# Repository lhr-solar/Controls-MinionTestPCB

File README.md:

# Controls-MinionTestPCB

[Quality Assurance Checklist(QUAC)](PULL_REQUEST_TEMPLATE.md)

[BOM](https://www.mouser.com/ProjectManager/ProjectDetail.aspx?AccessID=bacd2a80e1)

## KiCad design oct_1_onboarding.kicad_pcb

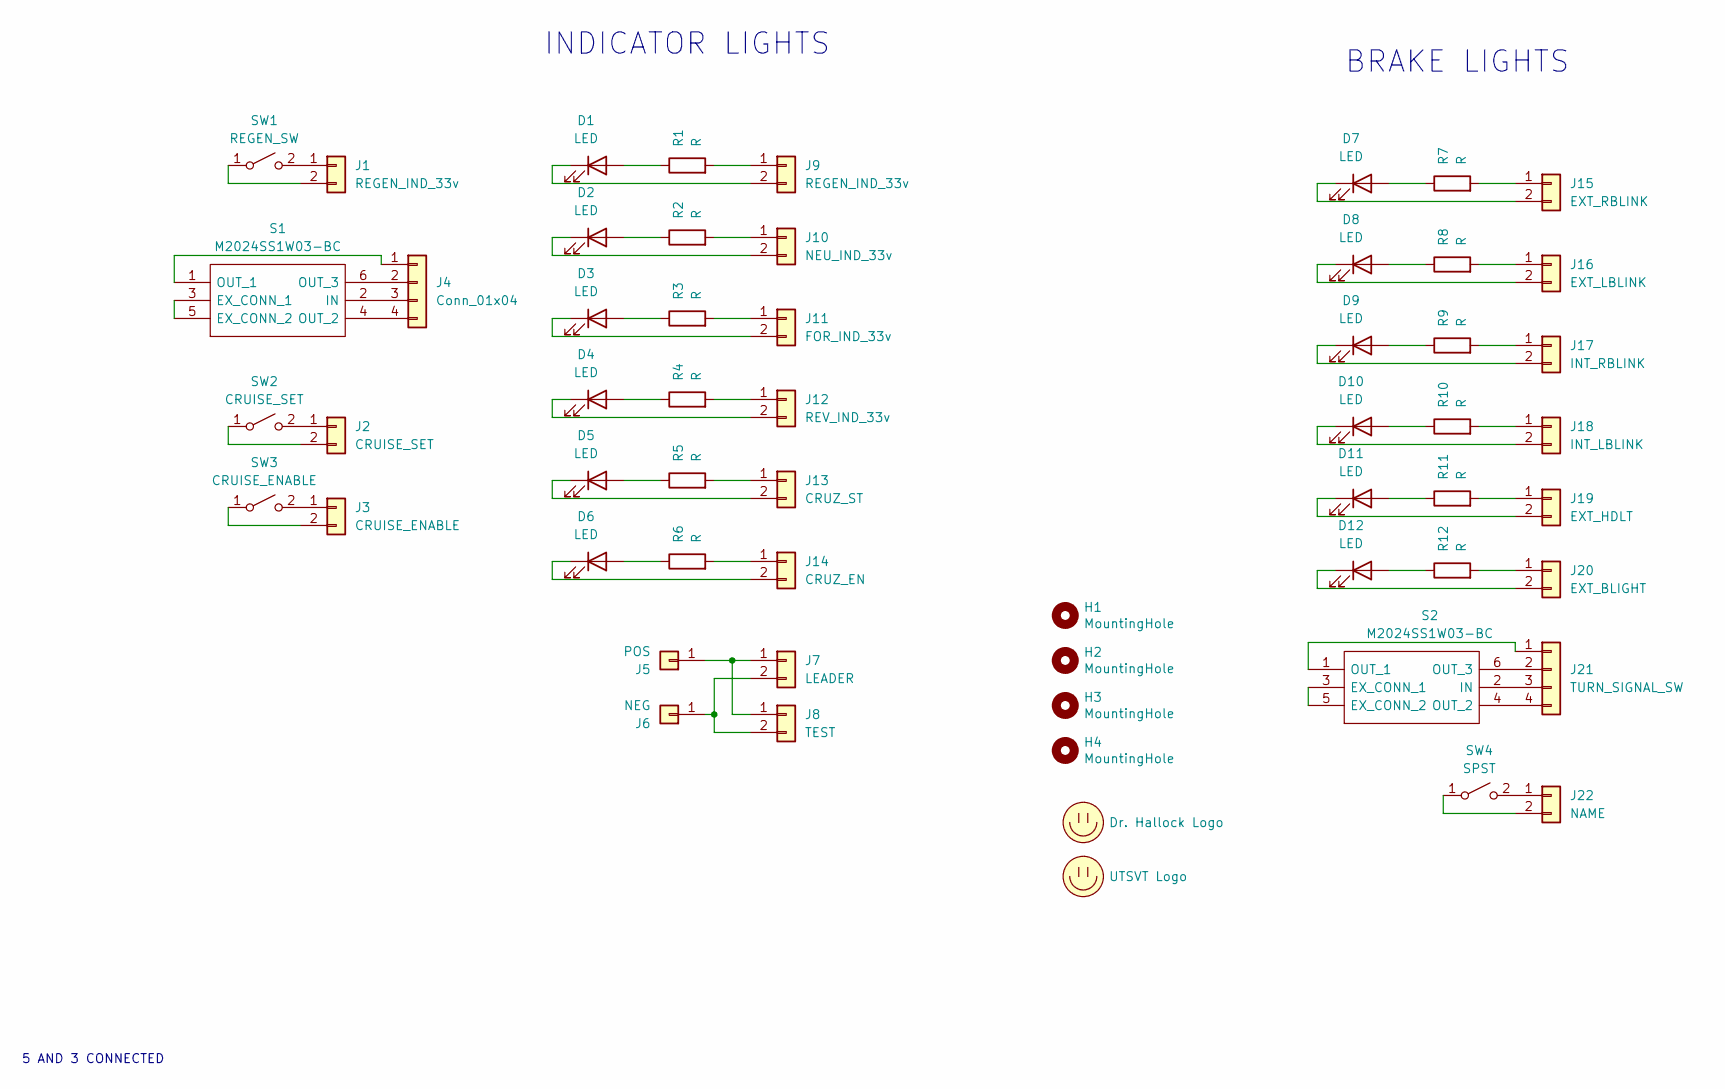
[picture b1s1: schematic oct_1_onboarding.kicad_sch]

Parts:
D1, D2, D3, D4, D5, D6, D7, D8, D9, D10, D11, D12: LED; LED_0805_2012Metric
H1, H2, H3, H4: MountingHole; MountingHole_3mm
J1, J9: REGEN_IND_33v; Molex_Micro-Fit_3.0_43650-0200_1x02_P3.00mm_Horizontal
J2: CRUISE_SET; Molex_Micro-Fit_3.0_43650-0200_1x02_P3.00mm_Horizontal
J3: CRUISE_ENABLE; Molex_Micro-Fit_3.0_43650-0200_1x02_P3.00mm_Horizontal
J4: Conn_01x04; Molex_Micro-Fit_3.0_43650-0400_1x04_P3.00mm_Horizontal
J5: POS; Banana_Jack_1_Pin_4mm
J6: NEG; Banana_Jack_1_Pin_4mm
J7: LEADER; Molex_Micro-Fit_3.0_43650-0200_1x02_P3.00mm_Horizontal
J8: TEST; Molex_Micro-Fit_3.0_43650-0200_1x02_P3.00mm_Horizontal
J10: NEU_IND_33v; Molex_Micro-Fit_3.0_43650-0200_1x02_P3.00mm_Horizontal
J11: FOR_IND_33v; Molex_Micro-Fit_3.0_43650-0200_1x02_P3.00mm_Horizontal
J12: REV_IND_33v; Molex_Micro-Fit_3.0_43650-0200_1x02_P3.00mm_Horizontal
J13: CRUZ_ST; Molex_Micro-Fit_3.0_43650-0200_1x02_P3.00mm_Horizontal
J14: CRUZ_EN; Molex_Micro-Fit_3.0_43650-0200_1x02_P3.00mm_Horizontal
J15: EXT_RBLINK; Molex_Micro-Fit_3.0_43650-0200_1x02_P3.00mm_Horizontal
J16: EXT_LBLINK; Molex_Micro-Fit_3.0_43650-0200_1x02_P3.00mm_Horizontal
J17: INT_RBLINK; Molex_Micro-Fit_3.0_43650-0200_1x02_P3.00mm_Horizontal
J18: INT_LBLINK; Molex_Micro-Fit_3.0_43650-0200_1x02_P3.00mm_Horizontal
J19: EXT_HDLT; Molex_Micro-Fit_3.0_43650-0200_1x02_P3.00mm_Horizontal
J20: EXT_BLIGHT; Molex_Micro-Fit_3.0_43650-0200_1x02_P3.00mm_Horizontal
J21: TURN_SIGNAL_SW; Molex_Micro-Fit_3.0_43650-0400_1x04_P3.00mm_Horizontal
J22: NAME; Molex_Micro-Fit_3.0_43650-0200_1x02_P3.00mm_Horizontal
LOGO1: Dr. Hallock Logo; Hallock_Image_Tiny
LOGO2: UTSVT Logo; UTSVT_Logo_Symbol
R1, R2, R3, R4, R5, R6, R7, R8, R9, R10, R11, R12: R; R_0805_2012Metric
S1, S2: M2024SS1W03-BC; M2024SS1W03BC; Mouser Part Number 633-M2024SS1W03-BC
SW1: REGEN_SW; 2MS6T1B3M2QES
SW2: CRUISE_SET; 2MS6T1B3M2QES
SW3: CRUISE_ENABLE; 2MS6T1B3M2QES
SW4: SPST; 2MS6T1B3M2QES

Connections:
unnamed: D1.1 (K), J9.2
unnamed: D1.2 (A), R1.1
unnamed: D2.1 (K), J10.2
unnamed: D2.2 (A), R2.1
unnamed: D3.1 (K), J11.2
unnamed: D3.2 (A), R3.1
unnamed: D4.1 (K), J12.2
unnamed: D4.2 (A), R4.1
unnamed: D5.1 (K), J13.2
unnamed: D5.2 (A), R5.1
unnamed: D6.1 (K), J14.2
unnamed: D6.2 (A), R6.1
unnamed: D7.1 (K), J15.2
unnamed: D7.2 (A), R7.1
unnamed: D8.1 (K), J16.2
unnamed: D8.2 (A), R8.1
unnamed: D9.1 (K), J17.2
unnamed: D9.2 (A), R9.1
unnamed: D10.1 (K), J18.2
unnamed: D10.2 (A), R10.1
unnamed: D11.1 (K), J19.2
unnamed: D11.2 (A), R11.1
unnamed: D12.1 (K), J20.2
unnamed: D12.2 (A), R12.1
unnamed: J1.1, SW1.2 (B)
unnamed: J1.2, SW1.1 (A)
unnamed: J2.1, SW2.2 (B)
unnamed: J2.2, SW2.1 (A)
unnamed: J3.1, SW3.2 (B)
unnamed: J3.2, SW3.1 (A)
unnamed: J4.1, S1.1 (OUT_1)
unnamed: J4.2, S1.6 (OUT_3)
unnamed: J4.3, S1.2 (IN)
unnamed: J4.4, S1.4 (OUT_2)
unnamed: J5.1, J7.1, J8.1
unnamed: J6.1, J7.2, J8.2
unnamed: J9.1, R1.2
unnamed: J10.1, R2.2
unnamed: J11.1, R3.2
unnamed: J12.1, R4.2
unnamed: J13.1, R5.2
unnamed: J14.1, R6.2
unnamed: J15.1, R7.2
unnamed: J16.1, R8.2
unnamed: J17.1, R9.2
unnamed: J18.1, R10.2
unnamed: J19.1, R11.2
unnamed: J20.1, R12.2
unnamed: J21.1, S2.1 (OUT_1)
unnamed: J21.2, S2.6 (OUT_3)
unnamed: J21.3, S2.2 (IN)
unnamed: J21.4, S2.4 (OUT_2)
unnamed: J22.1, SW4.2 (B)
unnamed: J22.2, SW4.1 (A)
unnamed: S1.3 (EX_CONN_1), S1.5 (EX_CONN_2)
unnamed: S2.3 (EX_CONN_1), S2.5 (EX_CONN_2)

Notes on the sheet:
INDICATOR LIGHTS
5 AND 3 CONNECTED
BRAKE LIGHTS

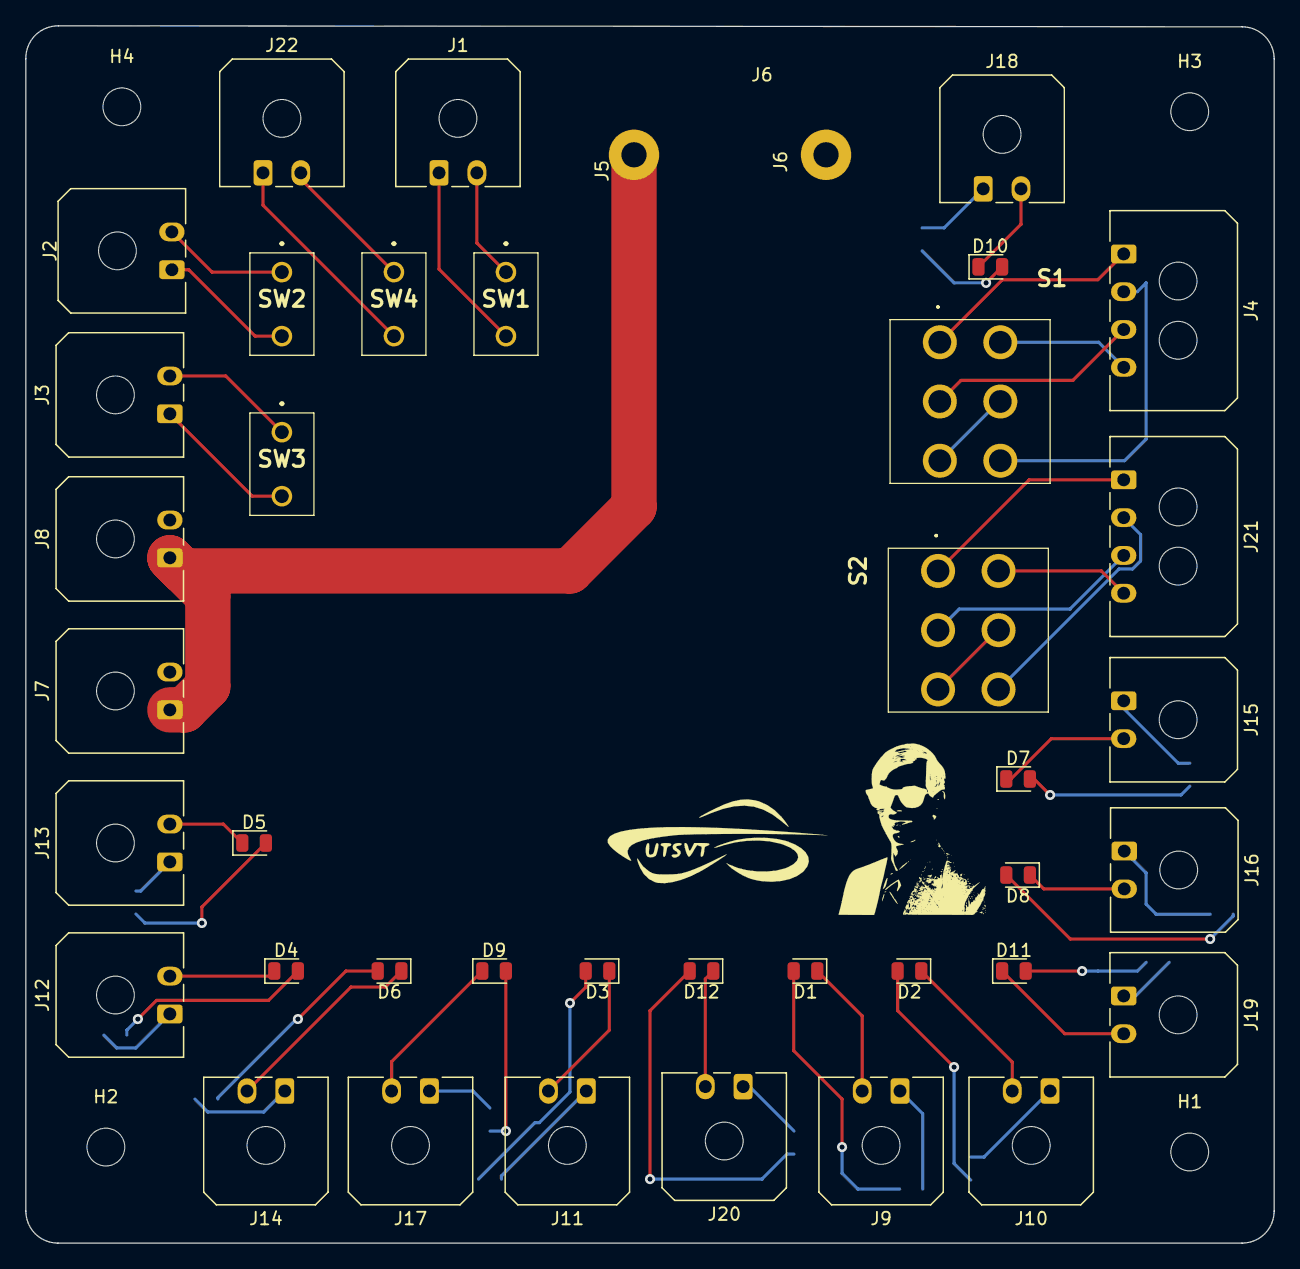
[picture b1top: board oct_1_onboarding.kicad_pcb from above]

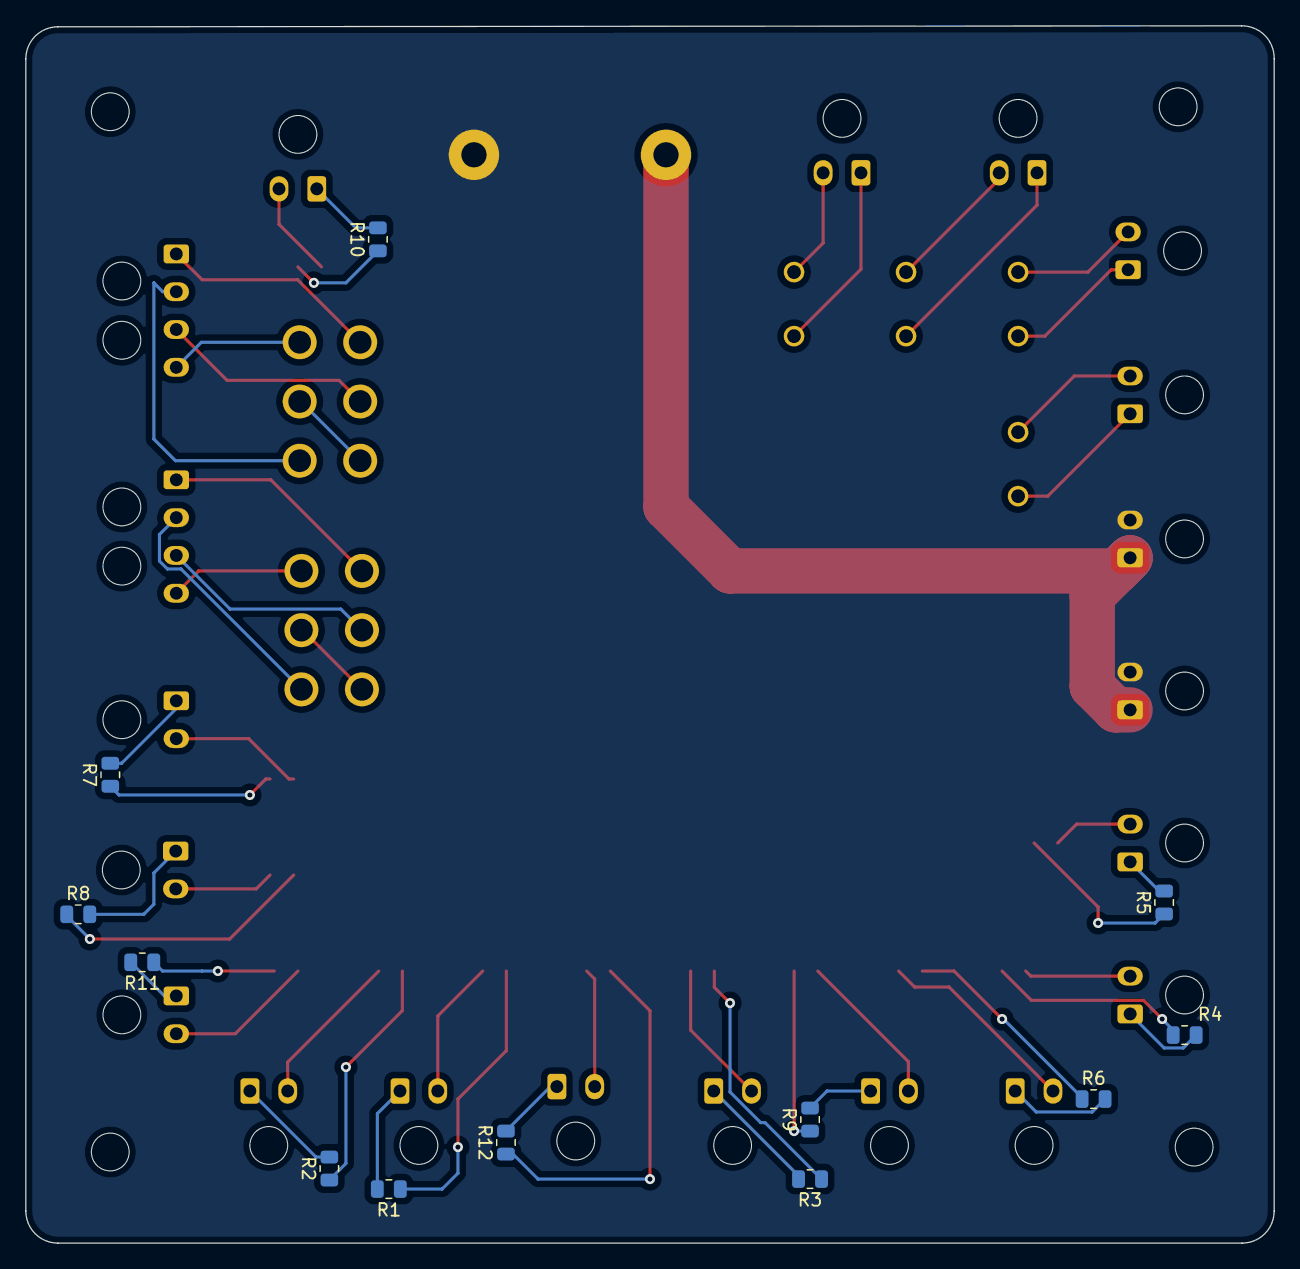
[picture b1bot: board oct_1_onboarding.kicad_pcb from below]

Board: 2 copper layers, 99.1 x 96.6 mm, 58 parts (12 on the bottom side), 56 nets.

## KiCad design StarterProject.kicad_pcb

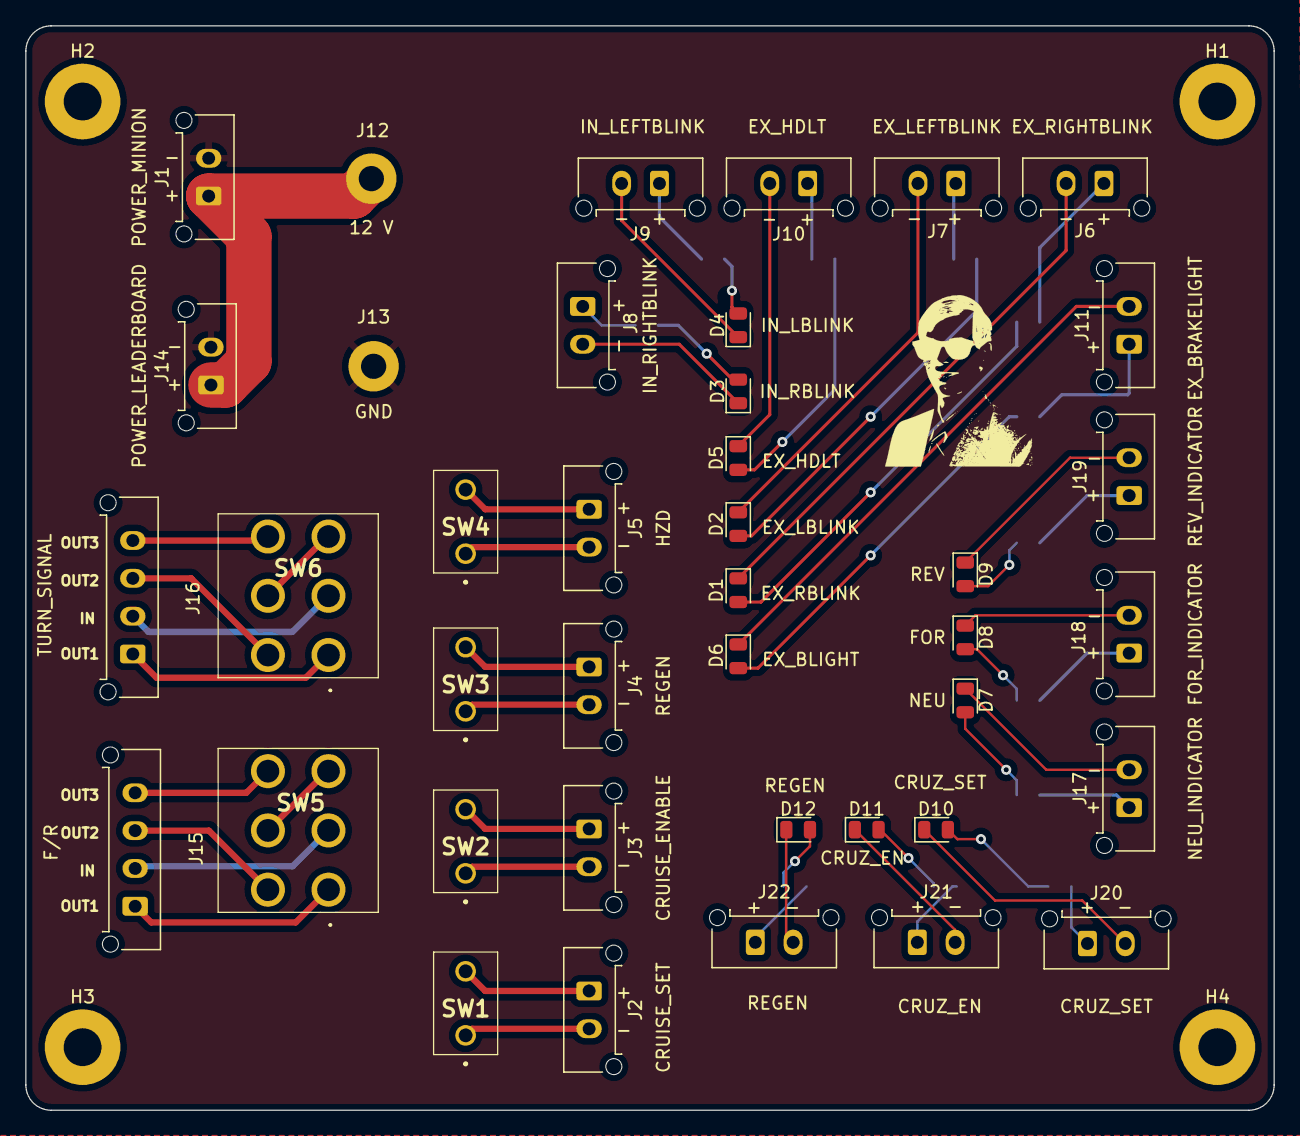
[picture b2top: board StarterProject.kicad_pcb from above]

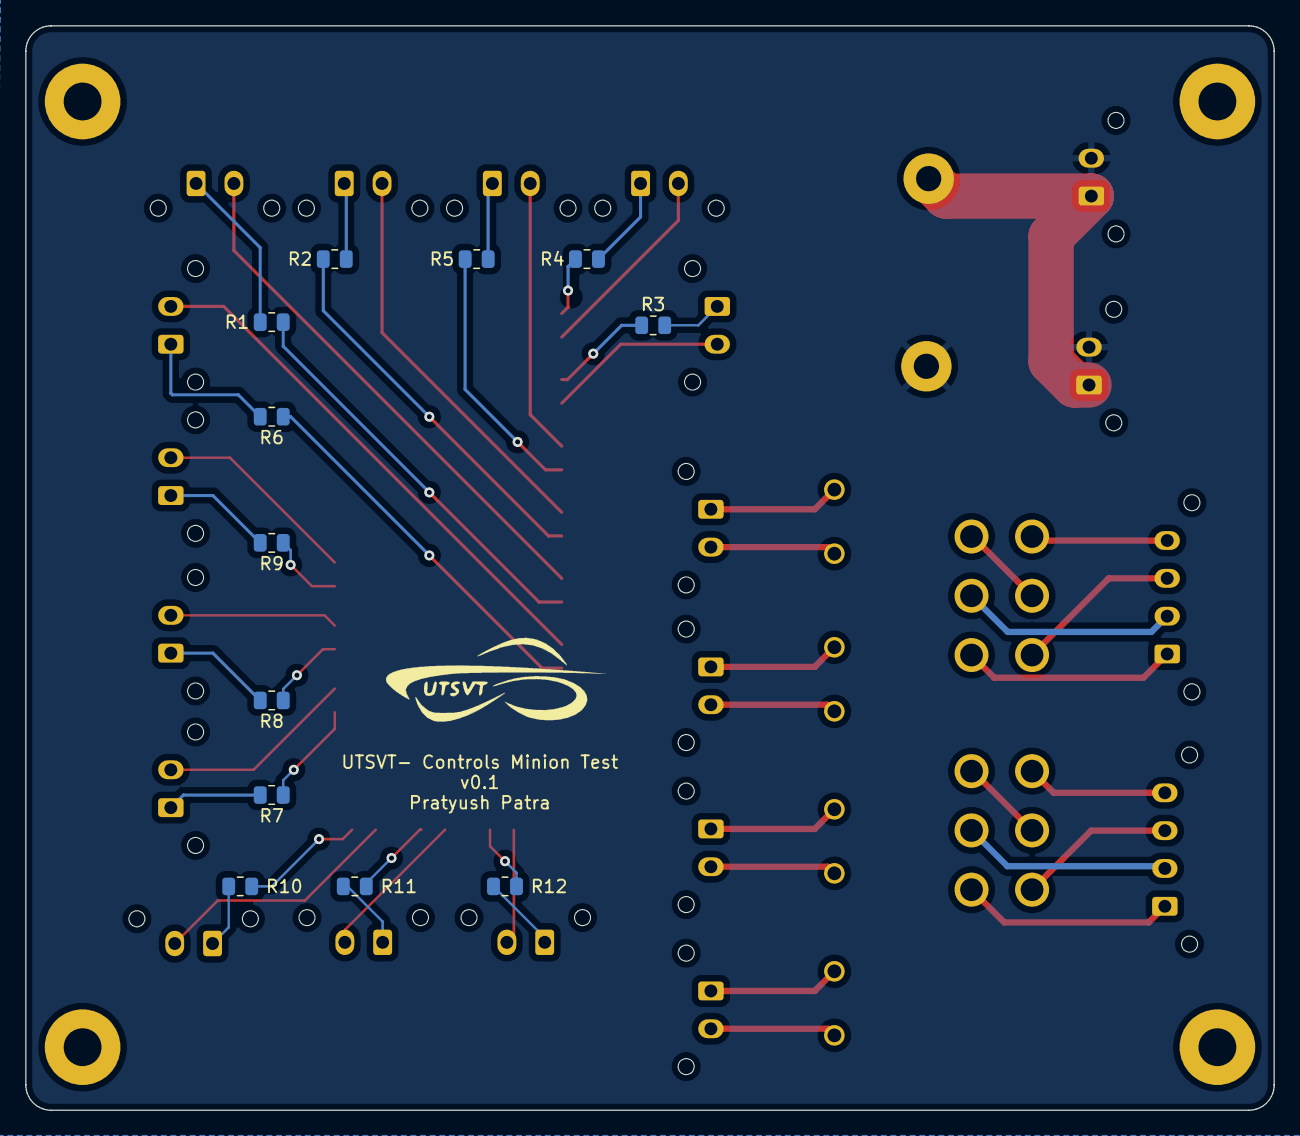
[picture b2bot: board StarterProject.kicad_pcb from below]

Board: 2 copper layers, 99.0 x 86.0 mm, 58 parts (13 on the bottom side), 56 nets.

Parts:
D1: EX_RBLINK; LED_0805_2012Metric
D2: EX_LBLINK; LED_0805_2012Metric
D3: IN_RBLINK; LED_0805_2012Metric
D4: IN_LBLINK; LED_0805_2012Metric
D5: EX_HDLT; LED_0805_2012Metric
D6: EX_BLIGHT; LED_0805_2012Metric
D7: NEU; LED_0805_2012Metric
D8: FOR; LED_0805_2012Metric
D9: REV; LED_0805_2012Metric
D10: CRUZ_SET; LED_0805_2012Metric
D11: CRUZ_EN; LED_0805_2012Metric
D12: REGEN; LED_0805_2012Metric
H1, H2, H3, H4: MountingHole; MountingHole_3mm_Pad
J1: POWER_MINION; Molex_Micro-Fit_3.0_43650-0215_1x02_P3.00mm_Vertical
J2: CRUISE_SET; Molex_Micro-Fit_3.0_43650-0215_1x02_P3.00mm_Vertical
J3: CRUISE_ENABLE; Molex_Micro-Fit_3.0_43650-0215_1x02_P3.00mm_Vertical
J4, J22: REGEN; Molex_Micro-Fit_3.0_43650-0215_1x02_P3.00mm_Vertical
J5: HZD; Molex_Micro-Fit_3.0_43650-0215_1x02_P3.00mm_Vertical
J6: EX_RIGHTBLINK; Molex_Micro-Fit_3.0_43650-0215_1x02_P3.00mm_Vertical
J7: EX_LEFTBLINK; Molex_Micro-Fit_3.0_43650-0215_1x02_P3.00mm_Vertical
J8: IN_RIGHTBLINK; Molex_Micro-Fit_3.0_43650-0215_1x02_P3.00mm_Vertical
J9: IN_LEFTBLINK; Molex_Micro-Fit_3.0_43650-0215_1x02_P3.00mm_Vertical
J10: EX_HDLT; Molex_Micro-Fit_3.0_43650-0215_1x02_P3.00mm_Vertical
J11: EX_BRAKELIGHT; Molex_Micro-Fit_3.0_43650-0215_1x02_P3.00mm_Vertical
J12: +12V; Banana_Jack_1_Pin_4mm
J13: GND; Banana_Jack_1_Pin_4mm
J14: POWER_LEADERBOARD; Molex_Micro-Fit_3.0_43650-0215_1x02_P3.00mm_Vertical
J15: F/R; Molex_Micro-Fit_3.0_43650-0415_1x04_P3.00mm_Vertical
J16: TURN_SIGNAL; Molex_Micro-Fit_3.0_43650-0415_1x04_P3.00mm_Vertical
J17: NEU_INDICATOR; Molex_Micro-Fit_3.0_43650-0215_1x02_P3.00mm_Vertical
J18: FOR_INDICATOR; Molex_Micro-Fit_3.0_43650-0215_1x02_P3.00mm_Vertical
J19: REV_INDICATOR; Molex_Micro-Fit_3.0_43650-0215_1x02_P3.00mm_Vertical
J20: CRUZ_SET; Molex_Micro-Fit_3.0_43650-0215_1x02_P3.00mm_Vertical
J21: CRUZ_EN; Molex_Micro-Fit_3.0_43650-0215_1x02_P3.00mm_Vertical
LOGO1: Logo_Placeholder; Hallock_Image_Tiny
LOGO2: Logo_Placeholder; UTSVT_Logo_Symbol
R1, R2, R3, R4, R5: 4.7k; R_0805_2012Metric
R6: 4,7k; R_0805_2012Metric
R7, R8, R9, R10, R11, R12: 330; R_0805_2012Metric
SW1: CRUISE_SET_SW; 2MS6T1B3M2QES
SW2: CRUISE_ENABLE_SW; 2MS6T1B3M2QES
SW3: REGEN_SW; 2MS6T1B3M2QES
SW4: HZD_SW; 2MS6T1B3M2QES
SW5: F/R; M2024SS1W03BC
SW6: TURN_SIGNAL_SW; M2024SS1W03BC

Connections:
GND: J1.2, J13.1, J14.2
unnamed: D1.1 (K), J6.2
unnamed: D1.2 (A), R1.1
unnamed: D2.1 (K), J7.2
unnamed: D2.2 (A), R2.1
unnamed: D3.1 (K), J8.2
unnamed: D3.2 (A), R3.1
unnamed: D4.1 (K), J9.2
unnamed: D4.2 (A), R4.1
unnamed: D5.1 (K), J10.2
unnamed: D5.2 (A), R5.1
unnamed: D6.1 (K), J11.2
unnamed: D6.2 (A), R6.1
unnamed: D7.1 (K), J17.2
unnamed: D7.2 (A), R7.1
unnamed: D8.1 (K), J18.2
unnamed: D8.2 (A), R8.1
unnamed: D9.1 (K), J19.2
unnamed: D9.2 (A), R9.1
unnamed: D10.1 (K), J20.2
unnamed: D10.2 (A), R10.1
unnamed: D11.1 (K), J21.2
unnamed: D11.2 (A), R11.1
unnamed: D12.1 (K), J22.2
unnamed: D12.2 (A), R12.1
unnamed: J1.1, J12.1, J14.1
unnamed: J2.1, SW1.2 (B)
unnamed: J2.2, SW1.1 (A)
unnamed: J3.1, SW2.2 (B)
unnamed: J3.2, SW2.1 (A)
unnamed: J4.1, SW3.2 (B)
unnamed: J4.2, SW3.1 (A)
unnamed: J5.1, SW4.2 (B)
unnamed: J5.2, SW4.1 (A)
unnamed: J6.1, R1.2
unnamed: J7.1, R2.2
unnamed: J8.1, R3.2
unnamed: J9.1, R4.2
unnamed: J10.1, R5.2
unnamed: J11.1, R6.2
unnamed: J15.1, SW5.1 (Out)
unnamed: J15.2, SW5.2 (In)
unnamed: J15.3, SW5.4 (Out)
unnamed: J15.4, SW5.6 (Out)
unnamed: J16.1, SW6.1 (Out)
unnamed: J16.2, SW6.2 (In)
unnamed: J16.3, SW6.4 (Out)
unnamed: J16.4, SW6.6 (Out)
unnamed: J17.1, R7.2
unnamed: J18.1, R8.2
unnamed: J19.1, R9.2
unnamed: J20.1, R10.2
unnamed: J21.1, R11.2
unnamed: J22.1, R12.2
unnamed: SW5.3 (Short), SW5.5 (Short)
unnamed: SW6.3 (Short), SW6.5 (Short)

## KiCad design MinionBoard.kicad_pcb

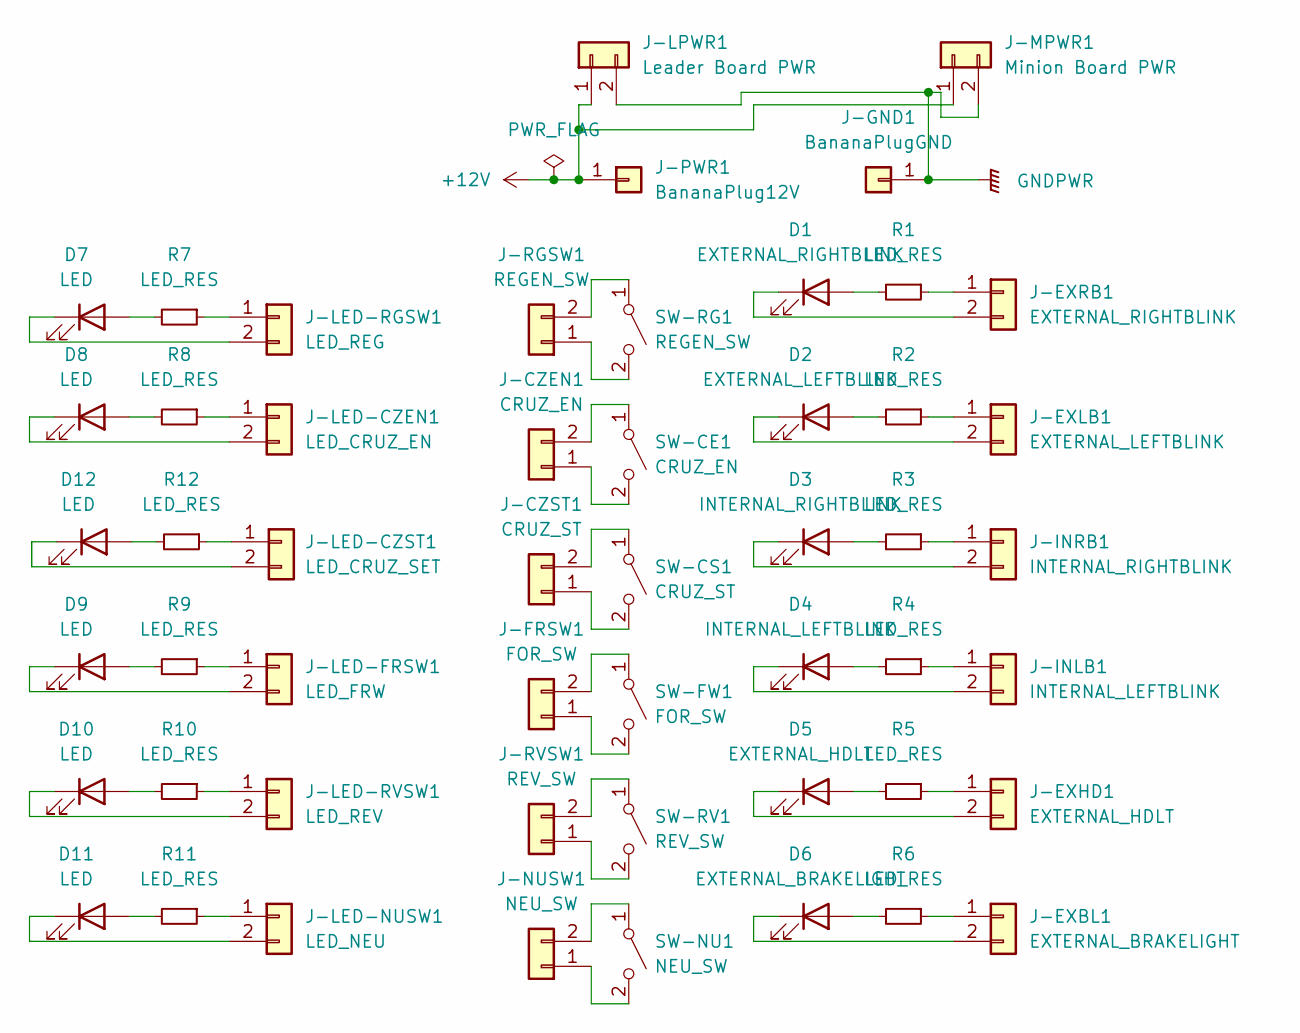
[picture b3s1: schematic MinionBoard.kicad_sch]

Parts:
D1: EXTERNAL_RIGHTBLINK; D_0805_2012Metric
D2: EXTERNAL_LEFTBLINK; D_0805_2012Metric
D3: INTERNAL_RIGHTBLINK; D_0805_2012Metric
D4: INTERNAL_LEFTBLINK; D_0805_2012Metric
D5: EXTERNAL_HDLT; D_0805_2012Metric
D6: EXTERNAL_BRAKELIGHT; D_0805_2012Metric
D7, D8, D9, D10, D11, D12: LED; D_0805_2012Metric
J-CZEN1: CRUZ_EN; Molex_MicroFit3.0_1x2xP3.00mm_PolarizingPeg_Vertical
J-CZST1: CRUZ_ST; Molex_MicroFit3.0_1x2xP3.00mm_PolarizingPeg_Vertical
J-EXBL1: EXTERNAL_BRAKELIGHT; Molex_MicroFit3.0_1x2xP3.00mm_PolarizingPeg_Vertical
J-EXHD1: EXTERNAL_HDLT; Molex_MicroFit3.0_1x2xP3.00mm_PolarizingPeg_Vertical
J-EXLB1: EXTERNAL_LEFTBLINK; Molex_MicroFit3.0_1x2xP3.00mm_PolarizingPeg_Vertical
J-EXRB1: EXTERNAL_RIGHTBLINK; Molex_MicroFit3.0_1x2xP3.00mm_PolarizingPeg_Vertical
J-FRSW1: FOR_SW; Molex_MicroFit3.0_1x2xP3.00mm_PolarizingPeg_Vertical
J-GND1: BananaPlugGND; Banana_Jack_1_Pin_4mm
J-INLB1: INTERNAL_LEFTBLINK; Molex_MicroFit3.0_1x2xP3.00mm_PolarizingPeg_Vertical
J-INRB1: INTERNAL_RIGHTBLINK; Molex_MicroFit3.0_1x2xP3.00mm_PolarizingPeg_Vertical
J-LED-CZEN1: LED_CRUZ_EN; Molex_MicroFit3.0_1x2xP3.00mm_PolarizingPeg_Vertical
J-LED-CZST1: LED_CRUZ_SET; Molex_MicroFit3.0_1x2xP3.00mm_PolarizingPeg_Vertical
J-LED-FRSW1: LED_FRW; Molex_MicroFit3.0_1x2xP3.00mm_PolarizingPeg_Vertical
J-LED-NUSW1: LED_NEU; Molex_MicroFit3.0_1x2xP3.00mm_PolarizingPeg_Vertical
J-LED-RGSW1: LED_REG; Molex_MicroFit3.0_1x2xP3.00mm_PolarizingPeg_Vertical
J-LED-RVSW1: LED_REV; Molex_MicroFit3.0_1x2xP3.00mm_PolarizingPeg_Vertical
J-LPWR1: Leader Board PWR; Molex_MicroFit3.0_1x2xP3.00mm_PolarizingPeg_Vertical
J-MPWR1: Minion Board PWR; Molex_MicroFit3.0_1x2xP3.00mm_PolarizingPeg_Vertical
J-NUSW1: NEU_SW; Molex_MicroFit3.0_1x2xP3.00mm_PolarizingPeg_Vertical
J-PWR1: BananaPlug12V; Banana_Jack_1_Pin_4mm
J-RGSW1: REGEN_SW; Molex_MicroFit3.0_1x2xP3.00mm_PolarizingPeg_Vertical
J-RVSW1: REV_SW; Molex_MicroFit3.0_1x2xP3.00mm_PolarizingPeg_Vertical
R1, R2, R3, R4, R5, R6, R7, R8, R9, R10, R11, R12: LED_RES; R_0805_2012Metric
SW-CE1: CRUZ_EN; 2MS6T1B3M2QES
SW-CS1: CRUZ_ST; 2MS6T1B3M2QES
SW-FW1: FOR_SW; 2MS6T1B3M2QES
SW-NU1: NEU_SW; 2MS6T1B3M2QES
SW-RG1: REGEN_SW; 2MS6T1B3M2QES
SW-RV1: REV_SW; 2MS6T1B3M2QES

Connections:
+12V: J-LPWR1.1, J-MPWR1.1, J-PWR1.1
GNDPWR: J-GND1.1, J-LPWR1.2, J-MPWR1.2
unnamed: D1.1 (K), J-EXRB1.2
unnamed: D1.2 (A), R1.2
unnamed: D2.1 (K), J-EXLB1.2
unnamed: D2.2 (A), R2.2
unnamed: D3.1 (K), J-INRB1.2
unnamed: D3.2 (A), R3.2
unnamed: D4.1 (K), J-INLB1.2
unnamed: D4.2 (A), R4.2
unnamed: D5.1 (K), J-EXHD1.2
unnamed: D5.2 (A), R5.2
unnamed: D6.1 (K), J-EXBL1.2
unnamed: D6.2 (A), R6.2
unnamed: D7.2 (A), R7.2
unnamed: D8.2 (A), R8.2
unnamed: D9.2 (A), R9.2
unnamed: D10.2 (A), R10.2
unnamed: D11.2 (A), R11.2
unnamed: D12.2 (A), R12.2
unnamed: J-CZEN1.1, SW-CE1.2 (B)
unnamed: J-CZEN1.2, SW-CE1.1 (A)
unnamed: J-CZST1.1, SW-CS1.2 (B)
unnamed: J-CZST1.2, SW-CS1.1 (A)
unnamed: J-EXBL1.1, R6.1
unnamed: J-EXHD1.1, R5.1
unnamed: J-EXLB1.1, R2.1
unnamed: J-EXRB1.1, R1.1
unnamed: J-FRSW1.1, SW-FW1.2 (B)
unnamed: J-FRSW1.2, SW-FW1.1 (A)
unnamed: J-INLB1.1, R4.1
unnamed: J-INRB1.1, R3.1
unnamed: J-LED-CZEN1.1, R8.1
unnamed: D8.1 (K), J-LED-CZEN1.2
unnamed: J-LED-CZST1.1, R12.1
unnamed: D12.1 (K), J-LED-CZST1.2
unnamed: J-LED-FRSW1.1, R9.1
unnamed: D9.1 (K), J-LED-FRSW1.2
unnamed: J-LED-NUSW1.1, R11.1
unnamed: D11.1 (K), J-LED-NUSW1.2
unnamed: J-LED-RGSW1.1, R7.1
unnamed: D7.1 (K), J-LED-RGSW1.2
unnamed: J-LED-RVSW1.1, R10.1
unnamed: D10.1 (K), J-LED-RVSW1.2
unnamed: J-NUSW1.1, SW-NU1.2 (B)
unnamed: J-NUSW1.2, SW-NU1.1 (A)
unnamed: J-RGSW1.1, SW-RG1.2 (B)
unnamed: J-RGSW1.2, SW-RG1.1 (A)
unnamed: J-RVSW1.1, SW-RV1.2 (B)
unnamed: J-RVSW1.2, SW-RV1.1 (A)

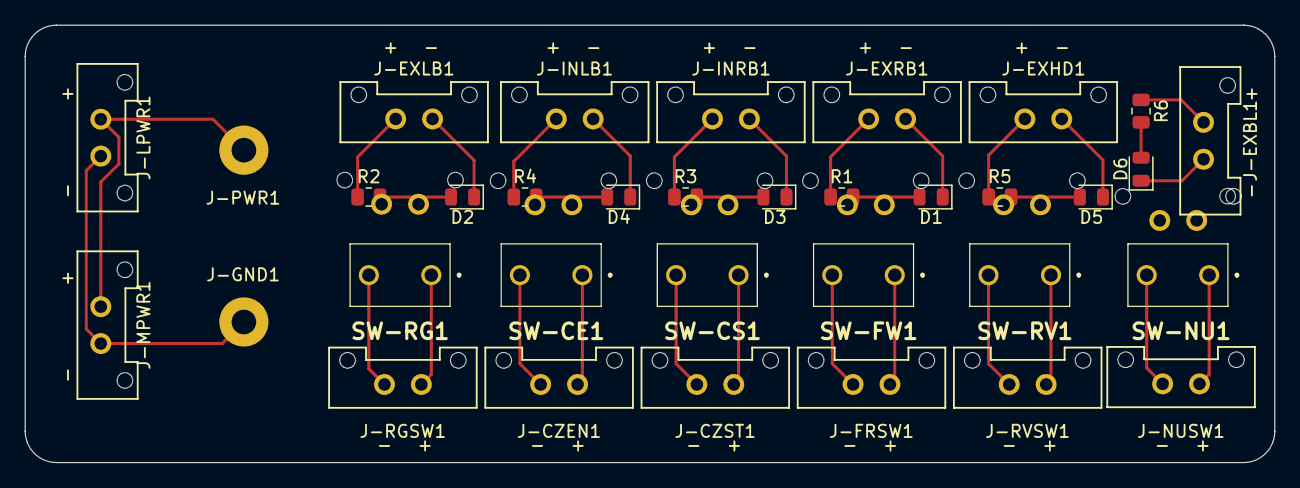
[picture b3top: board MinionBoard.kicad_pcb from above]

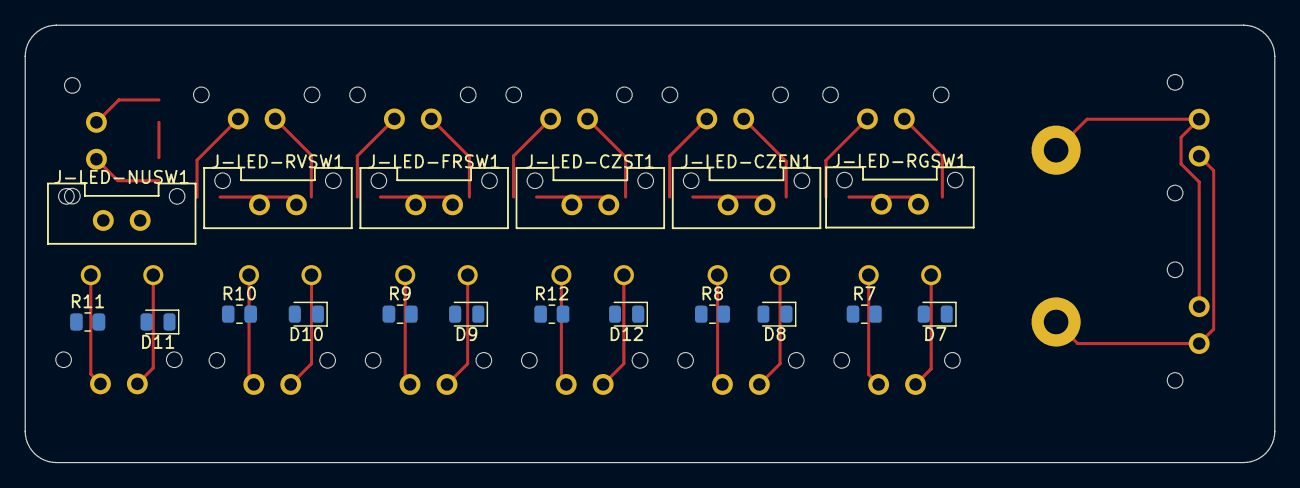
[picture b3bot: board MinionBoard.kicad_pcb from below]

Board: 2 copper layers, 101.6 x 35.6 mm, 52 parts (18 on the bottom side), 50 nets.

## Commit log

2022-09-24 Adds pcb part libraries
2022-09-24 Creates KICAD File
2022-09-24 Please enter the commit message for your changes. Lines starting
2022-10-01 Creates project files
2022-10-01 completed schematic and footprint
2022-10-01 Version One
2022-10-08 board update
2022-10-08 Is this working?
2022-10-08 update QUAC
2022-10-08 checklist wrap up, and ground plane added
2022-10-08 moved connectors to edge of board
2022-10-15 added BOM
2022-10-15 update spacing
2022-10-15 Updated PCB
2022-10-15 Labelling Update
2022-10-15 completed schematic and pcb ish
2022-10-15 added datasheets
